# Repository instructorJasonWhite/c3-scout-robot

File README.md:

# C3 Scout Robot

A small rover built around an ESP32-C3 SuperMini, two N20 gearmotors, one 18650 cell and a printed chassis. Build it, drive it from a browser, and add animated OLED faces or a matching storage case.

**Start with the [Scout builder guide](https://mechatronicsaint.com/c3-scout/index.html).**

[The Build](https://mechatronicsaint.com/c3-scout/build.html) · [The Board](https://mechatronicsaint.com/c3-scout/board.html) · [The Code](https://mechatronicsaint.com/c3-scout/code.html) · [The Accessories](https://mechatronicsaint.com/c3-scout/accessories.html)

## Current release

The four-part builder guide was published **21 October 2026**. The [complete robot wiring diagram](https://mechatronicsaint.com/c3-scout/build.html#complete-wiring) was added **25 October 2026**, with an [editable SVG](docs/builder-guide/assets/wiring/scout-complete-wiring.svg).

| Area | Current edition |
| --- | --- |
| Mechanics and printed robot parts | Rev B, all M3 hardware |
| Electronics and factory files | Carrier C v10 / Silk 03 |
| Browser control firmware | 19 October 2026 · SCOUT 2 / protocol 2 |
| Optional Android app | 1.2.0 |
| ScoutFaces Arduino library | 1.0.0 · ten animated expressions |
| Storage cases | Bumper, OLED and ESP32-CAM · all v8 |

Latest installation check: **27 October 2026**. The published 19 October firmware uploaded and started successfully, with browser control and OLED available, zero motor targets and both saved reverse flags retained. This was an upload/startup check. See the [Code guide](https://mechatronicsaint.com/c3-scout/code.html#last-device-check) and [recorded status](verification/Scout-Startup-Check-2026-10-27.json).

## Browse or download

GitHub displays HTML files as source. Use the live guide above for illustrated instructions, or clone/download this repository and run the following from its root:

```sh
python -m http.server 8000
```

Open [the local guide](http://localhost:8000/index.html). Keep the full folder layout together so images, downloads and technical references work offline.

- [Current firmware and software ZIP](06-Scout-Control/Scout-Control-Web-2026-10-19.zip) — firmware images, editable source, tests, technical guide and optional Android APK.
- [Complete technical control guide](https://mechatronicsaint.com/c3-scout/06-Scout-Control/CONTROL-GUIDE.html) — wiring, setup, protocol, calibration and recorded checks.
- [ScoutFaces 1.0.0 ZIP](06-Scout-Control/ScoutFaces-1.0.0.zip) — install in Arduino with **Sketch → Include Library → Add .ZIP Library**.
- [ScoutFaces source](libraries/ScoutFaces/) and complete [AutoCycle](libraries/ScoutFaces/examples/AutoCycle/AutoCycle.ino) / [SelectExpression](libraries/ScoutFaces/examples/SelectExpression/SelectExpression.ino) examples.

Each case package includes editable Fusion and STEP models, STL parts, Bambu P1S PLA projects, previews and print notes. Use the matching latch for the chosen variant.

| v8 case | Complete download | Native Fusion | STL and 3MF files |
| --- | --- | --- | --- |
| Bumper | [ZIP](08-Storage-Cases/Bumper/Scout-Bumper-Case-v8-Thin-Walls.zip) | [F3D](08-Storage-Cases/Bumper/Scout-Bumper-Case-v8.f3d) | [Files and print guide](08-Storage-Cases/Bumper/) |
| OLED | [ZIP](08-Storage-Cases/OLED/Scout-OLED-Case-v8-Thin-Walls.zip) | [F3D](08-Storage-Cases/OLED/Scout-OLED-Case-v8.f3d) | [Files and print guide](08-Storage-Cases/OLED/) |
| ESP32-CAM | [ZIP](08-Storage-Cases/ESP32-CAM/Scout-ESP32-CAM-Case-v8-Thin-Walls.zip) | [F3D](08-Storage-Cases/ESP32-CAM/Scout-ESP32-CAM-Case-v8.f3d) | [Files and print guide](08-Storage-Cases/ESP32-CAM/) |

## Load the firmware and drive

1. **Open RUN before connecting ESP USB.** Keep RUN open while programming or charging.
2. Install Arduino ESP32 core 3.x. Select **ESP32C3 Dev Module** and enable **USB CDC On Boot**.
3. Install **WebSockets 2.7.2**, Adafruit SSD1306/GFX and their dependencies, plus ScoutFaces. Follow [The Code](https://mechatronicsaint.com/c3-scout/code.html) for the matching build and upload instructions. The production sketch is [firmware/ScoutDrive](firmware/ScoutDrive/).
4. After uploading, unplug ESP USB, lift the wheels for the direction check, then close RUN.
5. Join Scout's Wi-Fi, open **http://192.168.4.1/** and press **Connect**. Start with the default 35% drive limit. Release the joystick to send zero; press **Stop** to end control. Reload the browser after updating firmware.

Motor directions are saved on the ESP. This Scout was tested with both reverse switches ON; a fresh or erased board defaults both OFF. Check directions with the wheels lifted and save the appropriate settings.

Browser control sends commands every 100 ms and has a 1000 ms ESP command cutoff. After command loss, motors may continue for up to one second. The optional Android app retains its 400 ms cutoff. Opening RUN cuts motor power independently of software.

## Editable software and documentation

Use the top-level folders for ongoing development:

| Source | Contents |
| --- | --- |
| [firmware/](firmware/) | Production ESP32-C3 sketch, embedded browser controller, OLED sketches and host tests |
| [libraries/ScoutFaces/](libraries/ScoutFaces/) | Reusable animated-face library and both examples |
| [android/](android/) | Optional native Android app and controller tests |
| [scripts/](scripts/) | Build, upload, packaging and verification helpers |
| [docs/](docs/) | Control notes and editable builder-guide content under `builder-guide/` |

[06-Scout-Control/source/](06-Scout-Control/source/) is the frozen source copy for the published 19 October software release. Its files accompany the downloadable guide and package. The top-level source folders are the canonical editable copies; release copies should be refreshed together when publishing another release.

Build helpers accept local tool paths where supported. See the guide and script parameters for the required Arduino, Java, Android and host-test tools. Building firmware does not upload it.

## Hardware files

| Folder | Contents |
| --- | --- |
| [01-Electronics-CarrierC](01-Electronics-CarrierC/) | Current schematic, board, library, PDFs, sourcing workbook and electrical checks; historical reviews are marked |
| [02-Mechanical-RevB](02-Mechanical-RevB/) | Full rover, chassis and populated mechanical board in Fusion and STEP formats |
| [03-Print-STL](03-Print-STL/) | Robot print parts, print notes and M3 fastener list |
| [04-Component-References](04-Component-References/) | Manufacturer datasheets, reference geometry and source notes |
| [05-Factory-CarrierC-v10](05-Factory-CarrierC-v10/) | Matching Gerbers, BOM, placement files and factory upload guide |
| [07-Bumper-Options](07-Bumper-Options/) | Optional OLED and ESP32-CAM bumper prototypes |
| [08-Storage-Cases](08-Storage-Cases/) | All three v8 case releases |

## Prototype status and provenance

Carrier C's electrical component placement has not been synchronized into the populated Rev B mechanical model. Check actual module, connector and fastener clearances before fabrication. Full v8 case fit and the optional bumper mounts still require physical verification. The ESP32-CAM mount includes no camera firmware or Scout camera power/control integration.

The factory guide records the checked Carrier C v10 release; use its matching files together. Electrical protection, motor stall current, supply startup and temperature still require prototype qualification. The circuit has no charge-and-run load sharing.

[PROJECT-MANIFEST.json](PROJECT-MANIFEST.json) records the published project files, hashes and revision status; [CURRENT-RELEASE.json](CURRENT-RELEASE.json) summarizes the editions. Manufacturer PDFs and reference models retain their original ownership. The Pololu model is a generic N20-family reference rather than verified geometry for the purchased Coliao motors; see [reference notes](04-Component-References/REFERENCE-NOTES.txt). No project-wide license has been selected.

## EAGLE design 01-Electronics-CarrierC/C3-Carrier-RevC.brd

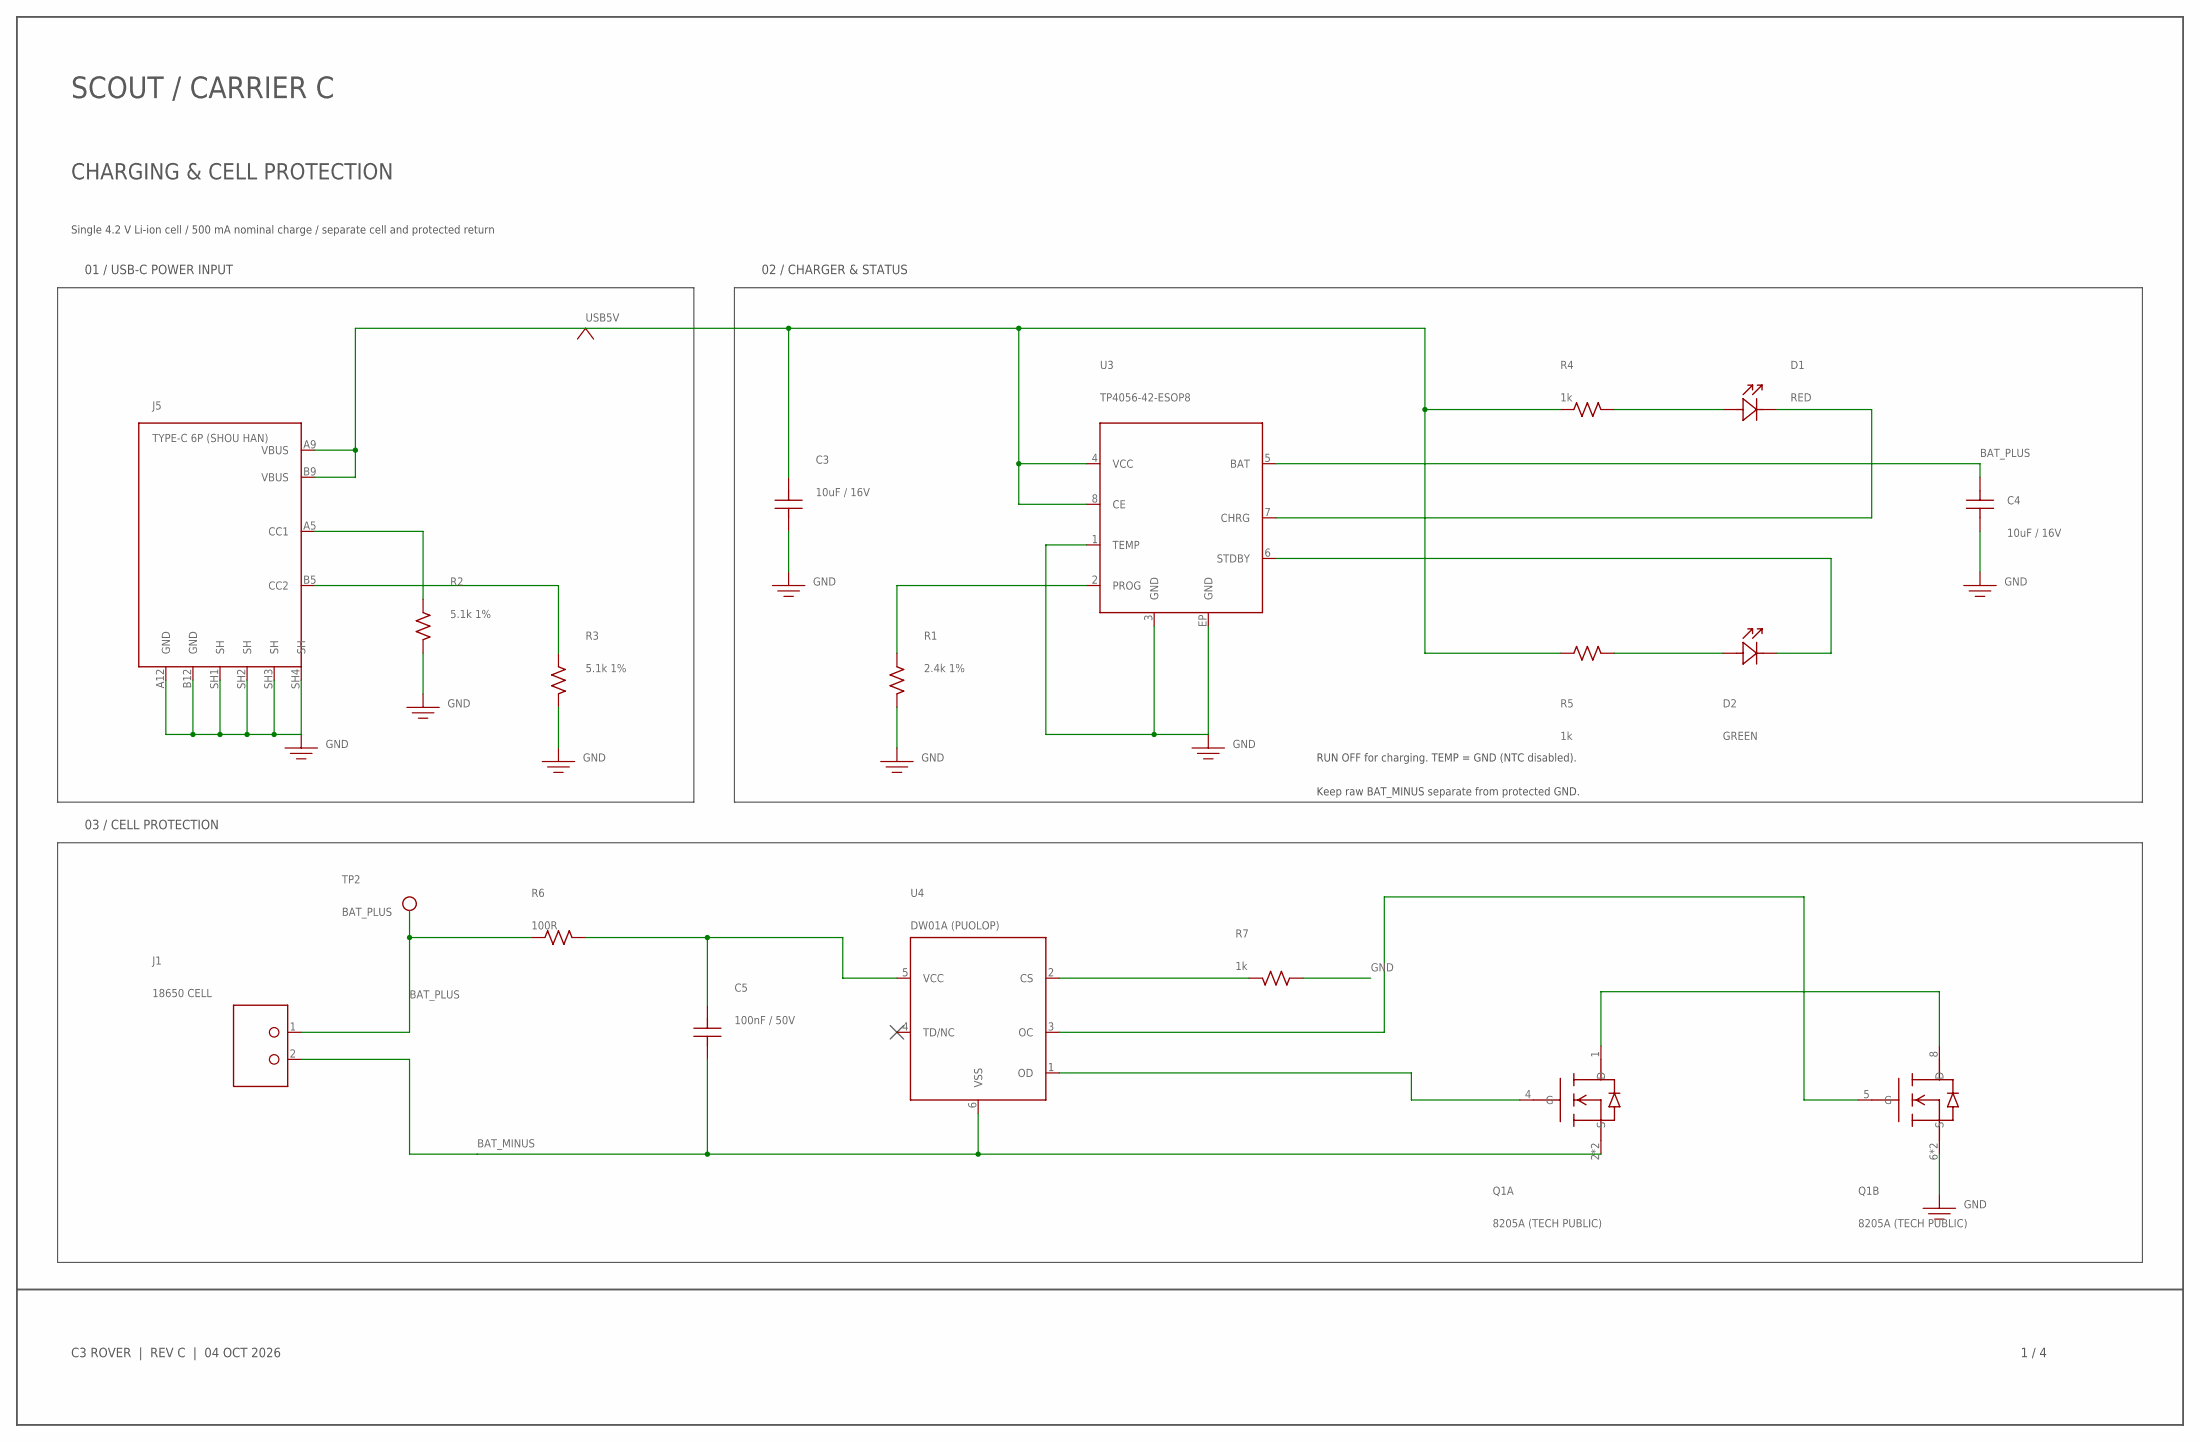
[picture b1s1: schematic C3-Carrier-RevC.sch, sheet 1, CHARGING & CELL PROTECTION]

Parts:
C3, C4: 10uF / 16V; C1206
C5: 100nF / 50V; C0805
D1: RED; LED0805
D2: GREEN; LED0805
J1: 18650 CELL; WIRE2-3.5
J5: TYPE-C 6P (SHOU HAN); USB-C-SHOUHAN-6P-C456012
Q1: 8205A (TECH PUBLIC); TSSOP8-0.65
R1: 2.4k 1%; R0805
R2, R3: 5.1k 1%; R0805
R4, R5, R7: 1k; R0805
R6: 100R; R0805
TP2: BAT_PLUS; TESTPAD
U3: TP4056-42-ESOP8; ESOP8-EP
U4: DW01A (PUOLOP); SOT23-6

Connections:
BAT_MINUS: C5.2, J1.2, Q1.2 (S), Q1.3 (S), U4.6 (VSS)
BAT_PLUS: C4.1, J1.1, R6.1, TP2.1, U3.5 (BAT); also elsewhere on the board
CC1: J5.A5 (CC1), R2.1
CC2: J5.B5 (CC2), R3.1
CHRG: D1.2, U3.7 (CHRG)
CHRG_LED: D1.1, R4.2
CS: R7.2, U4.2 (CS)
D12: Q1.1 (D), Q1.8 (D)
DW_VCC: C5.1, R6.2, U4.5 (VCC)
FULL_LED: D2.1, R5.2
GND: C3.2, C4.2, J5.A12 (GND), J5.B12 (GND), J5.SH1 (SH), J5.SH2 (SH), J5.SH3 (SH), J5.SH4 (SH), Q1.6 (S), Q1.7 (S), R1.2, R2.2, R3.2, R7.1, U3.1 (TEMP), U3.3 (GND), U3.EP (GND); also elsewhere on the board
OC: Q1.5 (G), U4.3 (OC)
OD: Q1.4 (G), U4.1 (OD)
PROG: R1.1, U3.2 (PROG)
STDBY: D2.2, U3.6 (STDBY)
USB5V: C3.1, J5.A9 (VBUS), J5.B9 (VBUS), R4.1, R5.1, U3.4 (VCC), U3.8 (CE)

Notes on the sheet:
SCOUT / CARRIER C
CHARGING & CELL PROTECTION
Single 4.2 V Li-ion cell / 500 mA nominal charge / separate cell and protected return
C3 ROVER | REV C | 04 OCT 2026
1 / 4
01 / USB-C POWER INPUT
02 / CHARGER & STATUS
03 / CELL PROTECTION
RUN OFF for charging. TEMP = GND (NTC disabled).
Keep raw BAT_MINUS separate from protected GND.

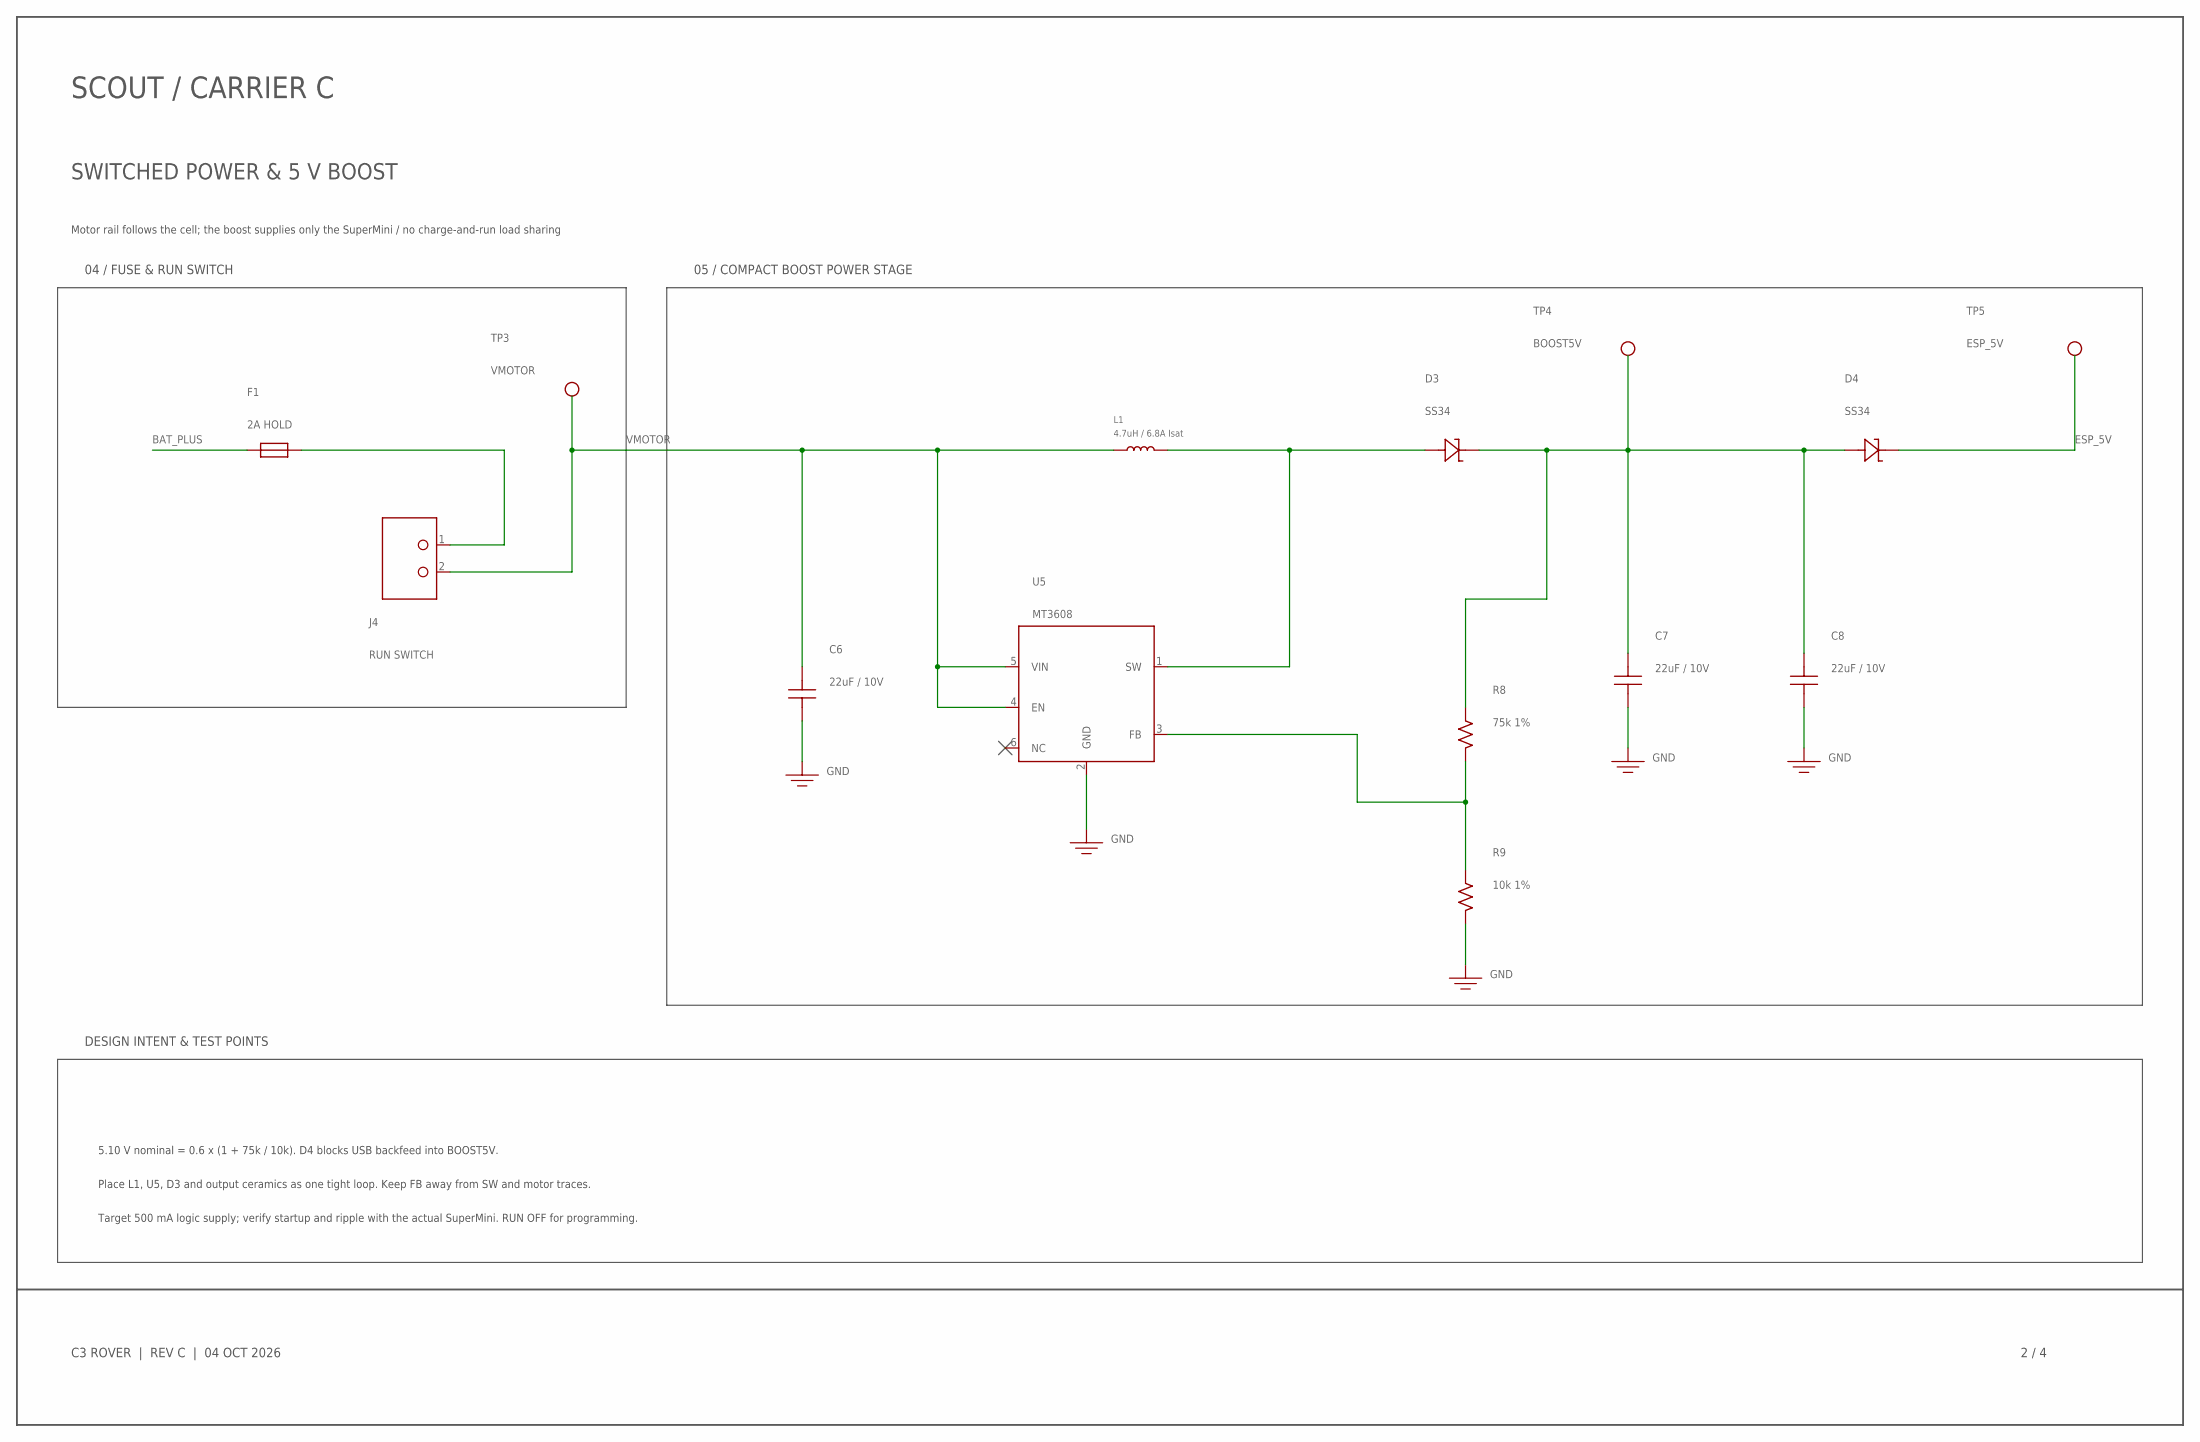
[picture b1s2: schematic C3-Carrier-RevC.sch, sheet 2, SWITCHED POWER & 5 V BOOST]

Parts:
C6, C7, C8: 22uF / 10V; C1206
D3, D4: SS34; SMA
F1: 2A HOLD; F1812
J4: RUN SWITCH; WIRE2-3.5
L1: 4.7uH / 6.8A Isat; L6
R8: 75k 1%; R0805
R9: 10k 1%; R0805
TP3: VMOTOR; TESTPAD
TP4: BOOST5V; TESTPAD
TP5: ESP_5V; TESTPAD
U5: MT3608; SOT23-6

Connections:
BAT_PLUS: F1.1; also elsewhere on the board
BOOST5V: C7.1, C8.1, D3.1, D4.2, R8.1, TP4.1
ESP_5V: D4.1, TP5.1; also elsewhere on the board
FB: R8.2, R9.1, U5.3 (FB)
FUSED_BAT: F1.2, J4.1
GND: C6.2, C7.2, C8.2, R9.2, U5.2 (GND); also elsewhere on the board
SW: D3.2, L1.2, U5.1 (SW)
VMOTOR: C6.1, J4.2, L1.1, TP3.1, U5.4 (EN), U5.5 (VIN); also elsewhere on the board

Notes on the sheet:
SCOUT / CARRIER C
SWITCHED POWER & 5 V BOOST
Motor rail follows the cell; the boost supplies only the SuperMini / no charge-and-run load sharing
C3 ROVER | REV C | 04 OCT 2026
2 / 4
04 / FUSE & RUN SWITCH
05 / COMPACT BOOST POWER STAGE
DESIGN INTENT & TEST POINTS
5.10 V nominal = 0.6 x (1 + 75k / 10k). D4 blocks USB backfeed into BOOST5V.
Place L1, U5, D3 and output ceramics as one tight loop. Keep FB away from SW and motor traces.
Target 500 mA logic supply; verify startup and ripple with the actual SuperMini. RUN OFF for programming.

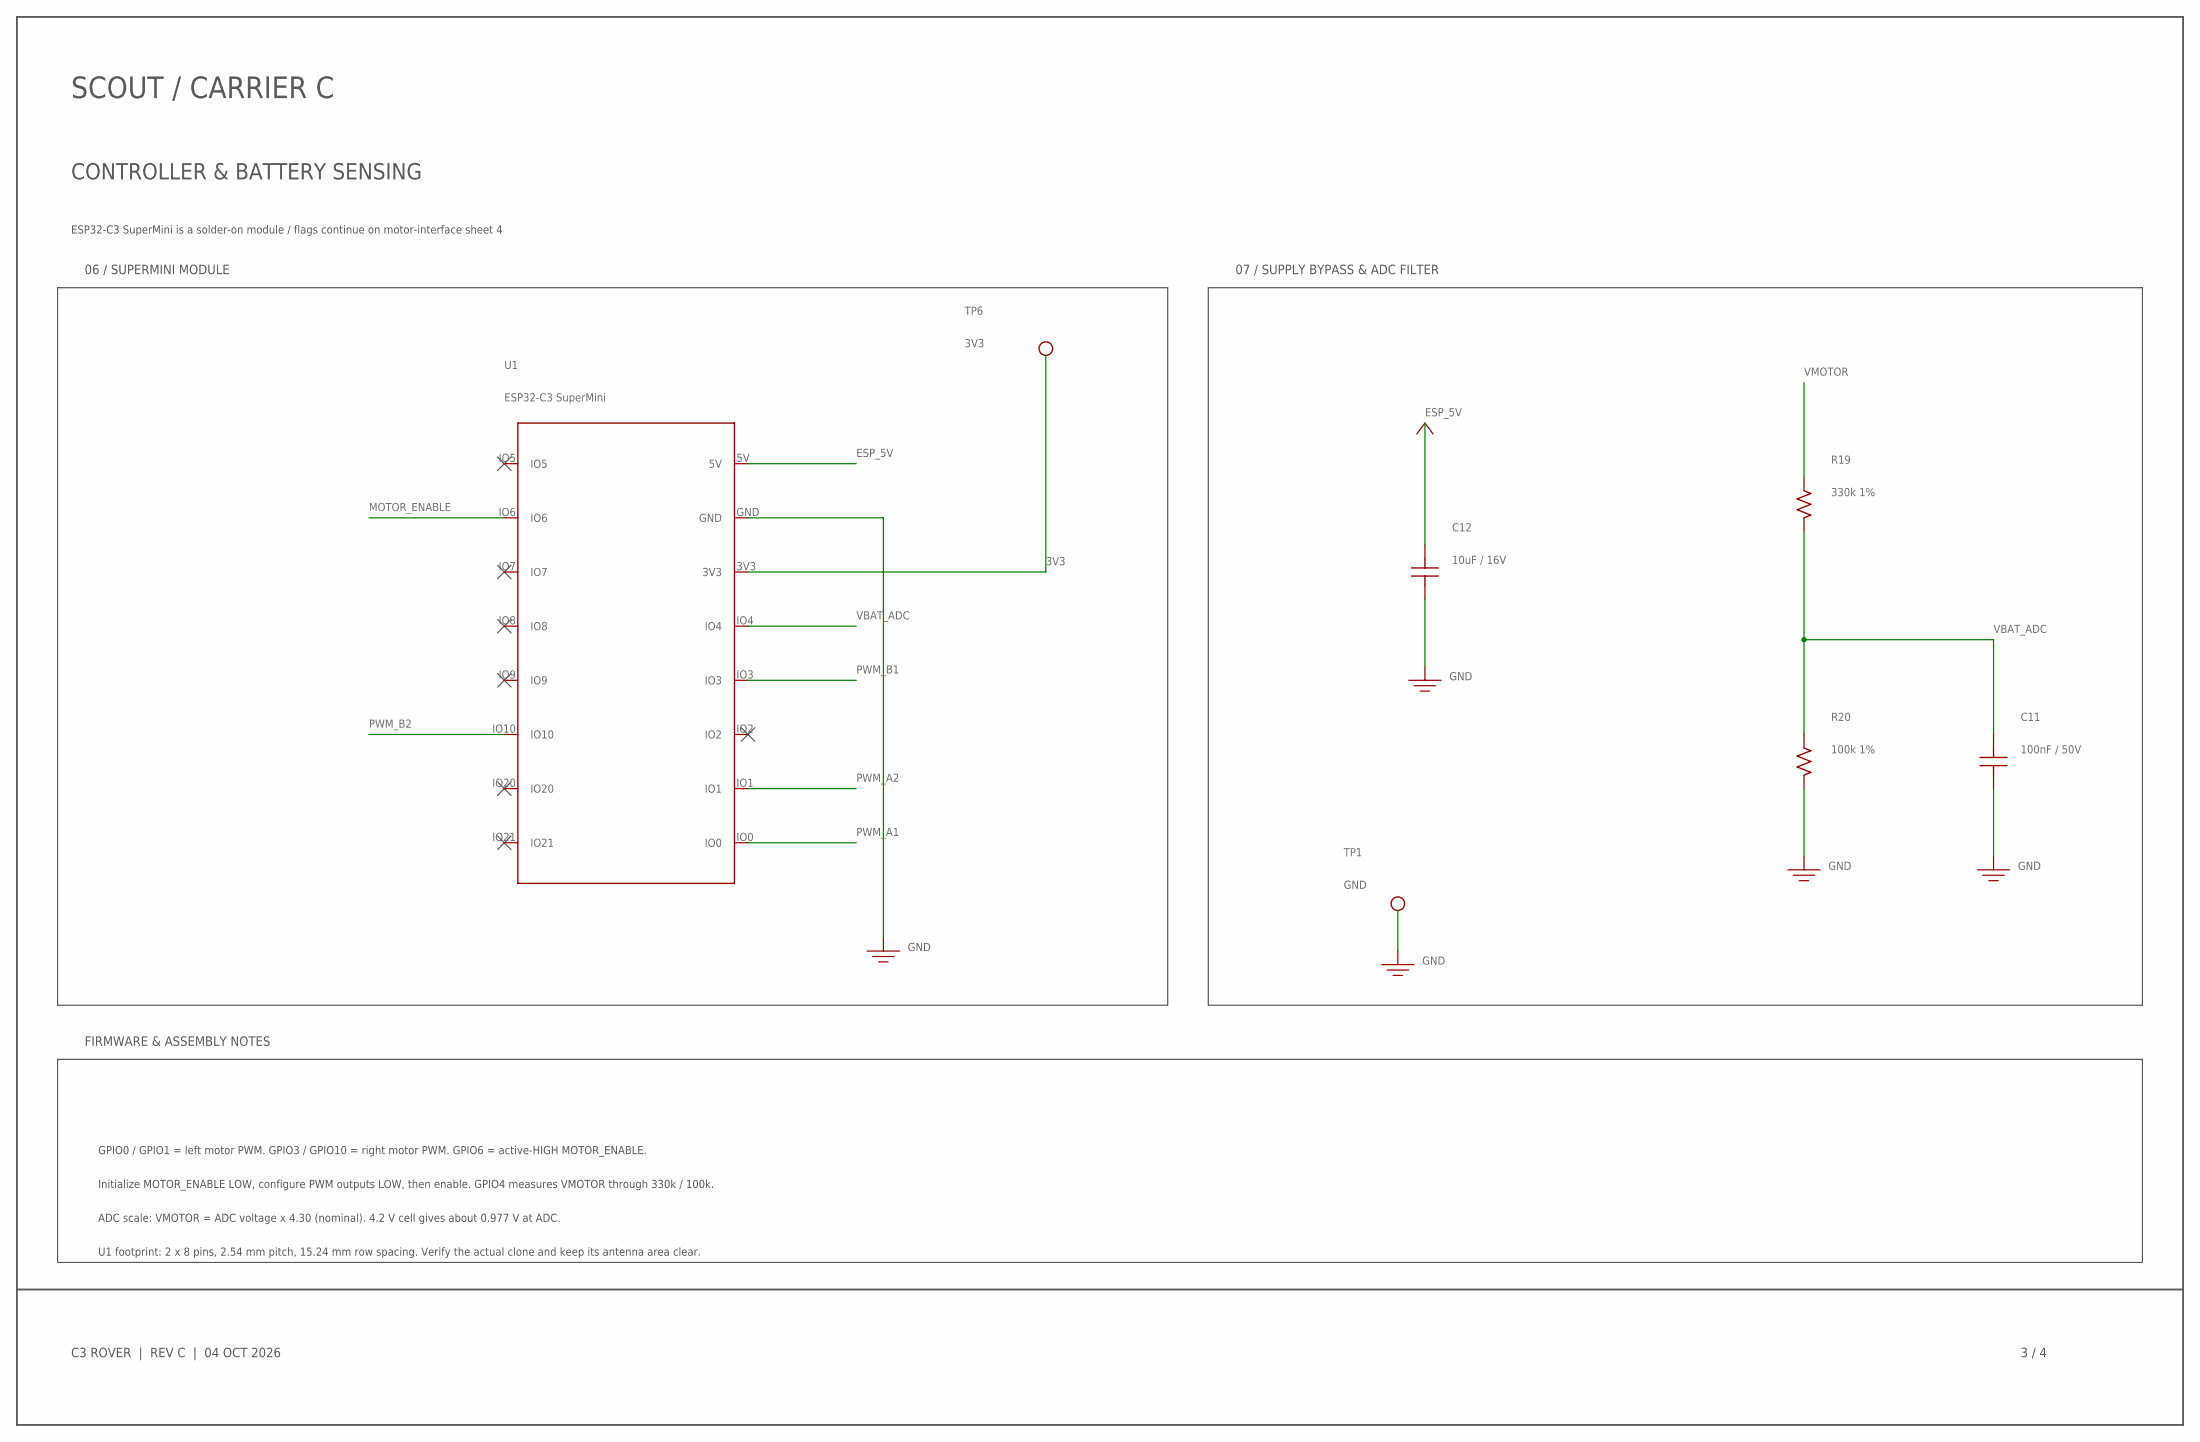
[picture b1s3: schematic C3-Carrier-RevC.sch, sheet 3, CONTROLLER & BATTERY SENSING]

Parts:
C11: 100nF / 50V; C0805
C12: 10uF / 16V; C1206
R19: 330k 1%; R0805
R20: 100k 1%; R0805
TP1: GND; TESTPAD
TP6: 3V3; TESTPAD
U1: ESP32-C3 SuperMini; SUPERMINI-2X8-15.24

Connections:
3V3: TP6.1, U1.3V3; also elsewhere on the board
ESP_5V: C12.1, U1.5V; also elsewhere on the board
GND: C11.2, C12.2, R20.2, TP1.1, U1.GND; also elsewhere on the board
MOTOR_ENABLE: U1.IO6; also elsewhere on the board
PWM_A1: U1.IO0; also elsewhere on the board
PWM_A2: U1.IO1; also elsewhere on the board
PWM_B1: U1.IO3; also elsewhere on the board
PWM_B2: U1.IO10; also elsewhere on the board
VBAT_ADC: C11.1, R19.2, R20.1, U1.IO4
VMOTOR: R19.1; also elsewhere on the board

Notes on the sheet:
SCOUT / CARRIER C
CONTROLLER & BATTERY SENSING
ESP32-C3 SuperMini is a solder-on module / flags continue on motor-interface sheet 4
C3 ROVER | REV C | 04 OCT 2026
3 / 4
06 / SUPERMINI MODULE
07 / SUPPLY BYPASS & ADC FILTER
FIRMWARE & ASSEMBLY NOTES
GPIO0 / GPIO1 = left motor PWM. GPIO3 / GPIO10 = right motor PWM. GPIO6 = active-HIGH MOTOR_ENABLE.
Initialize MOTOR_ENABLE LOW, configure PWM outputs LOW, then enable. GPIO4 measures VMOTOR through 330k / 100k.
ADC scale: VMOTOR = ADC voltage x 4.30 (nominal). 4.2 V cell gives about 0.977 V at ADC.
U1 footprint: 2 x 8 pins, 2.54 mm pitch, 15.24 mm row spacing. Verify the actual clone and keep its antenna area clear.

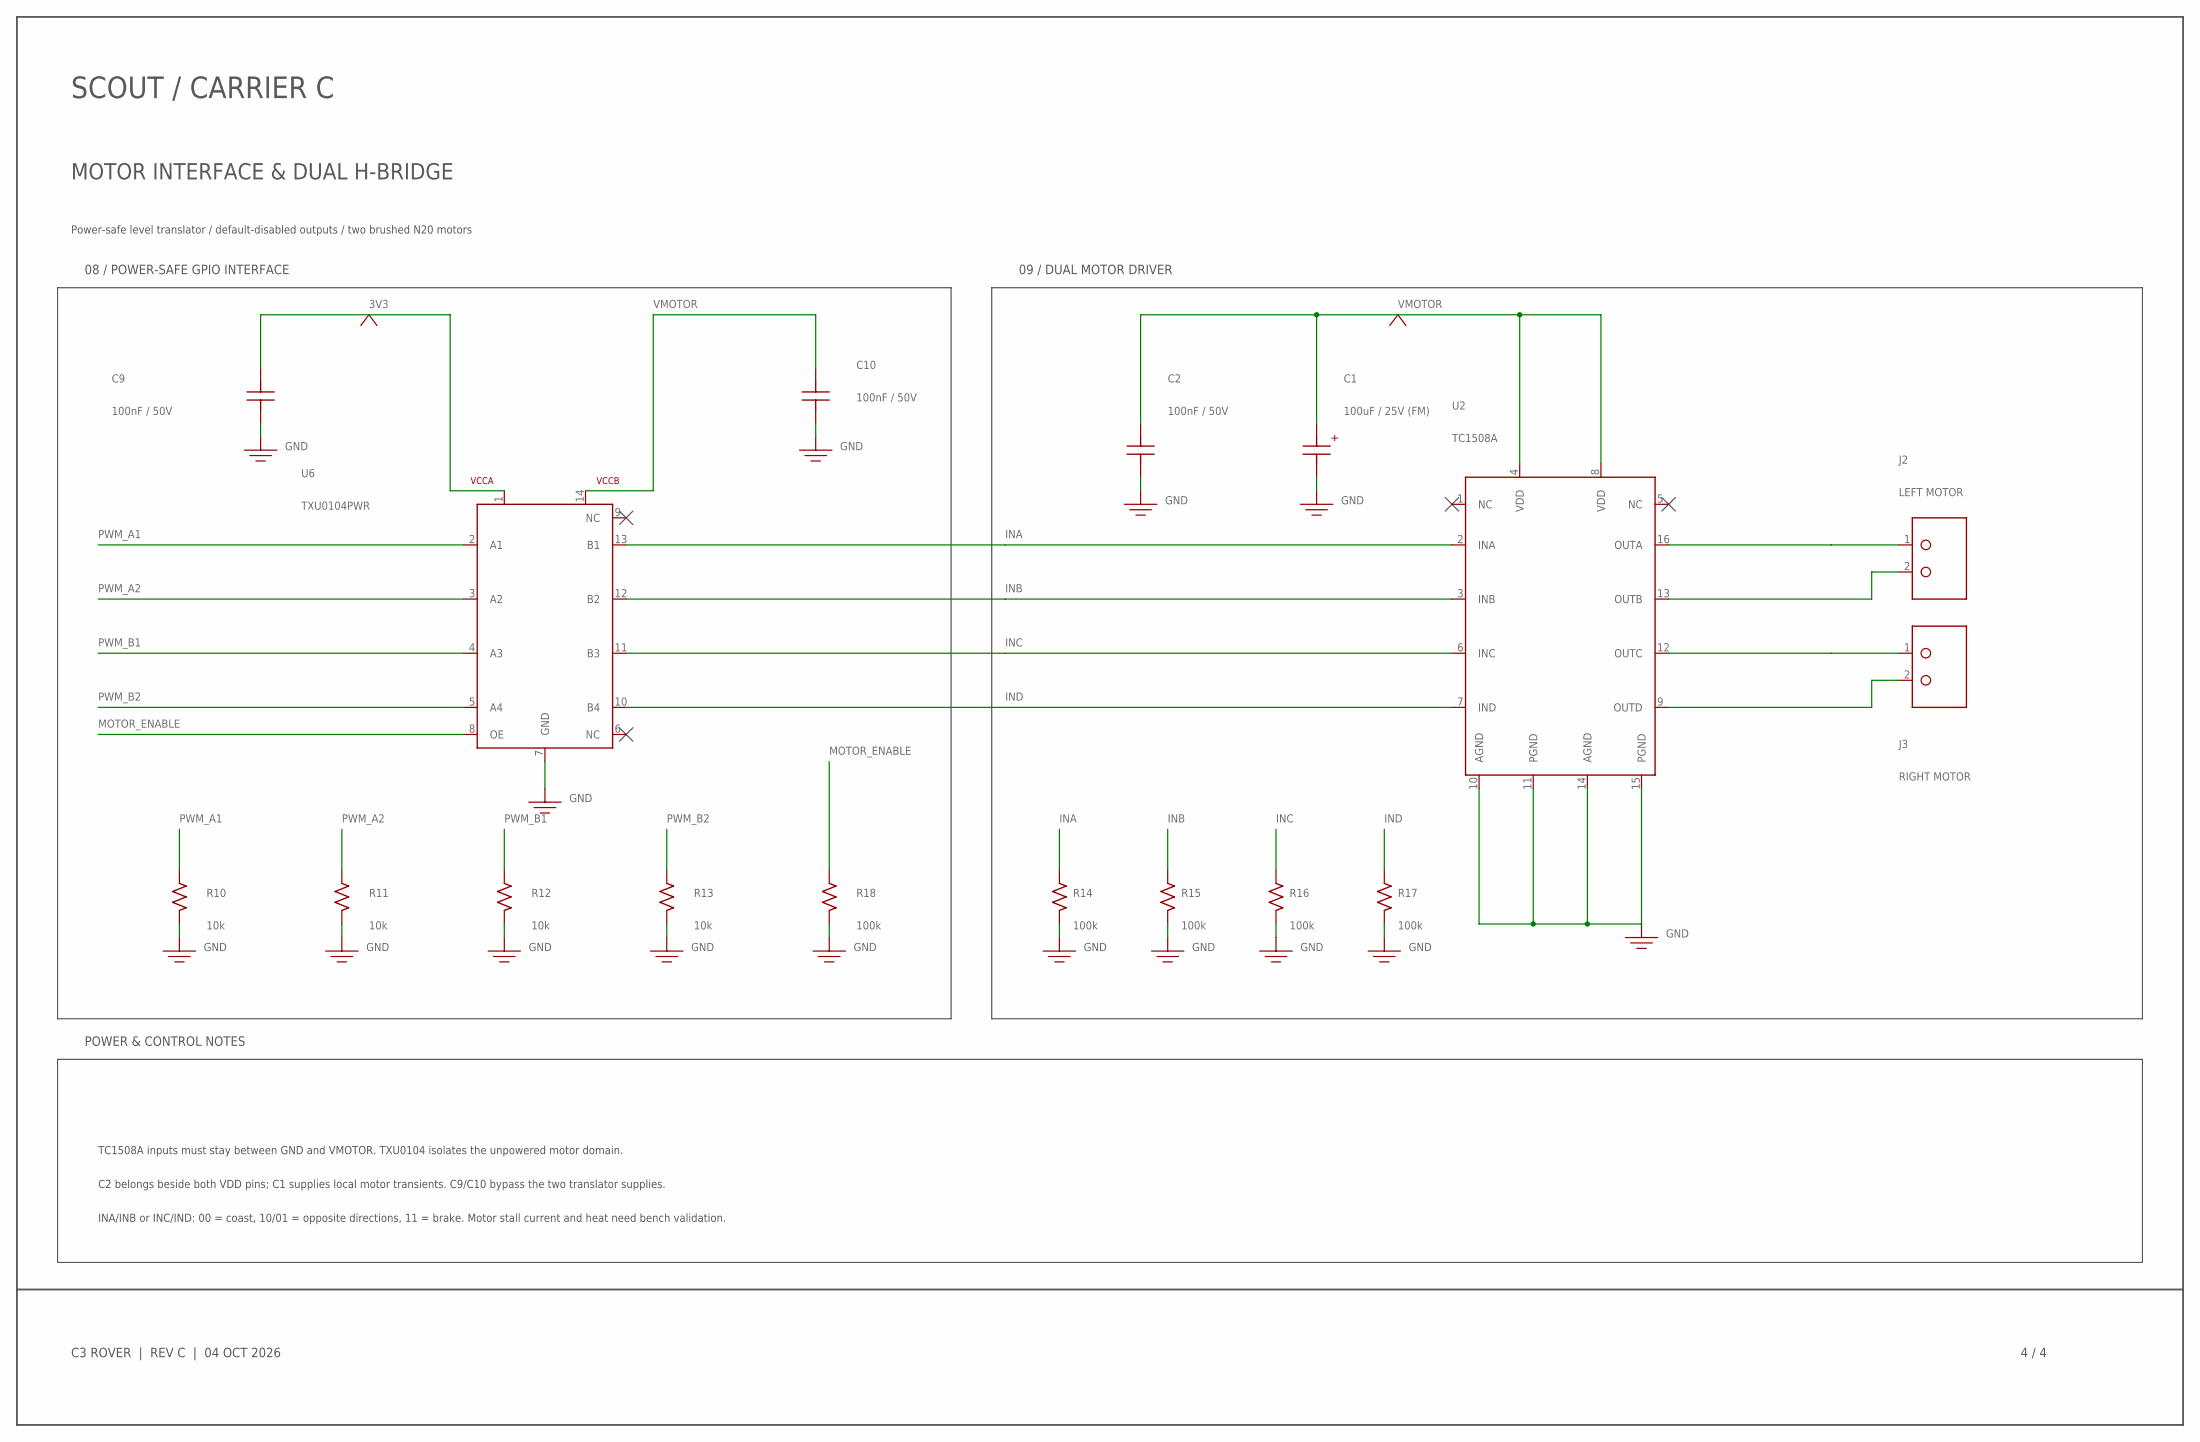
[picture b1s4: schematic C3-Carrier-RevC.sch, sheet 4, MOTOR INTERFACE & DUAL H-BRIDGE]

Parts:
C1: 100uF / 25V (FM); RADIAL-6.3-2.5
C2, C9, C10: 100nF / 50V; C0805
J2: LEFT MOTOR; WIRE2-3.5
J3: RIGHT MOTOR; WIRE2-3.5
R10, R11, R12, R13: 10k; R0805
R14, R15, R16, R17, R18: 100k; R0805
U2: TC1508A; SOIC16-1.27
U6: TXU0104PWR; TSSOP14-0.65

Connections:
3V3: C9.1, U6.1 (VCCA); also elsewhere on the board
GND: C1.2, C2.2, C9.2, C10.2, R10.2, R11.2, R12.2, R13.2, R14.2, R15.2, R16.2, R17.2, R18.2, U2.10 (AGND), U2.11 (PGND), U2.14 (AGND), U2.15 (PGND), U6.7 (GND); also elsewhere on the board
INA: R14.1, U2.2 (INA), U6.13 (B1)
INB: R15.1, U2.3 (INB), U6.12 (B2)
INC: R16.1, U2.6 (INC), U6.11 (B3)
IND: R17.1, U2.7 (IND), U6.10 (B4)
MOTOR_A1: J2.1, U2.16 (OUTA)
MOTOR_A2: J2.2, U2.13 (OUTB)
MOTOR_B1: J3.1, U2.12 (OUTC)
MOTOR_B2: J3.2, U2.9 (OUTD)
MOTOR_ENABLE: R18.1, U6.8 (OE); also elsewhere on the board
PWM_A1: R10.1, U6.2 (A1); also elsewhere on the board
PWM_A2: R11.1, U6.3 (A2); also elsewhere on the board
PWM_B1: R12.1, U6.4 (A3); also elsewhere on the board
PWM_B2: R13.1, U6.5 (A4); also elsewhere on the board
VMOTOR: C1.1, C2.1, C10.1, U2.4 (VDD), U2.8 (VDD), U6.14 (VCCB); also elsewhere on the board

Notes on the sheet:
SCOUT / CARRIER C
MOTOR INTERFACE & DUAL H-BRIDGE
Power-safe level translator / default-disabled outputs / two brushed N20 motors
C3 ROVER | REV C | 04 OCT 2026
4 / 4
08 / POWER-SAFE GPIO INTERFACE
09 / DUAL MOTOR DRIVER
POWER & CONTROL NOTES
TC1508A inputs must stay between GND and VMOTOR. TXU0104 isolates the unpowered motor domain.
C2 belongs beside both VDD pins; C1 supplies local motor transients. C9/C10 bypass the two translator supplies.
INA/INB or INC/IND: 00 = coast, 10/01 = opposite directions, 11 = brake. Motor stall current and heat need bench validation.

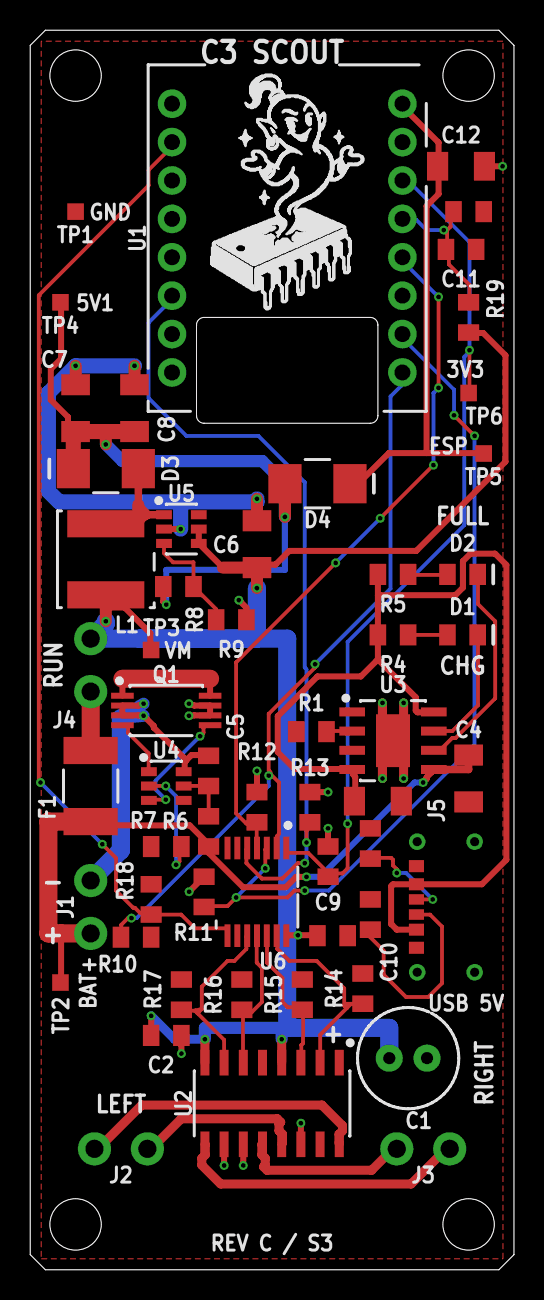
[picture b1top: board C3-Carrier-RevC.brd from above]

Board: 2 copper layers, 32.0 x 82.0 mm, 56 parts (0 on the bottom side), 37 nets.

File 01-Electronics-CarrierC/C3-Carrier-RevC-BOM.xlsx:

Carrier C sourcing BOM
46 fitted components / 45 factory assembly / 1 user module / reviewed 2026-10-05
Catalog listings are not stock reservations. JLC placement rotations require as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
References | Qty | Specification | Package | Manufacturer | MPN | LCSC / JLC code | Assembly category | Availability evidence |  | Source | Assembly notes
U1 | 1 | ESP32-C3 SuperMini | 2 x 8 / 2.54 mm | User module | ESP32-C3 SuperMini |  | Hand solder | User supplied |  |  | Verify clone pinout and 15.24 mm row spacing. Antenna over cutout; component si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
U2 | 1 | Dual motor driver | SOP-16 | Shenzhen Fuman | TC1508A | C5142992 | Extended | JLC catalog confirmed; stock not verified |  | https://jlcpcb.com/partdetail/Shenzhen_FumanElec-TC1508A/C5142992 | Validate actual N20 stall current and package temperature.
U3 | 1 | 500 mA charger | ESOP-8 with exposed pad | Top Power | TP4056-42-ESOP8 | C16581 | Extended | JLC catalog confirmed; stock not verified |  | https://jlcpcb.com/partdetail/TP4056-42-ESOP8/C16581 | R1 = 2.4 kohm. RUN OFF while charging. TEMP grounded; no cell-temperature sensi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
U4 | 1 | Cell protection | SOT-23-6 | PUOLOP | DW01A | C351410 | Extended | JLC stock verified 2026-10-05; user selected |  | https://jlcpcb.com/partdetail/DW01A/C351410 | Pin-compatible SOT-23-6; 2.5 V cutoff / 2.9 V recovery, 150 mV current sense. A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
Q1 | 1 | Dual common-drain N-MOSFET | TSSOP-8 | TECH PUBLIC | 8205A | C7419210 | Extended | JLC stock verified 2026-10-05; user selected |  | https://jlcpcb.com/partdetail/TECHPUBLIC-8205A/C7419210 | TSSOP-8, common drain at pins 1/8. Lower RDS(on) raises overcurrent trip curren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
U5 | 1 | 5.10 V boost | SOT-23-6 | Aerosemi | MT3608 | C84817 | Extended | JLC catalog confirmed; stock not verified |  | https://jlcpcb.com/partdetail/C84817 | Nominal 0.6 x (1 + 75k/10k). D4 drop precedes SuperMini 5V input.
U6 | 1 | 4-channel level translator | TSSOP-14 | Texas Instruments | TXU0104PWR | C2938871 | Extended | JLC catalog confirmed; stock not verified |  | https://jlcpcb.com/partdetail/TexasInstruments-TXU0104PWR/C2938871 | OE pulled low; separates 3V3 control from switched motor domain.
L1 | 1 | 4.7 uH / 4.5 A Irms / 6.8 A Isat | 6 x 6 x 4.5 mm max | Bourns | SRN6045TA-4R7M | C2044594 | Extended | JLC catalog confirmed; stock not verified |  | https://jlcpcb.com/partdetail/BOURNS-SRN6045TA4R7M/C2044594 | Manufacturer land pattern: 5.1 x 1.8 mm pads, 4.7 mm centers. Footprint updated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
D3, D4 | 2 | SS34 / 3 A / 40 V | SMA | MDD | SS34 | C8678 | Basic | JLC catalog confirmed; stock not verified |  | https://jlcpcb.com/partdetail/Mdd-SS34/C8678 | Pad 1 = cathode.
F1 | 1 | 2 A hold / 16 V PTC | 1812 | Littelfuse | 1812L200/16DR | C439873 | Extended | JLC catalog confirmed; stock not verified |  | https://jlcpcb.com/partdetail/Littelfuse-1812L20016DR/C439873 | 3.5 A trip rating; temperature derating applies.
D1 | 1 | Red indicator | 0805 | NationStar | NCD0805R1 | C84256 | Basic | JLC catalog confirmed; stock not verified |  | https://jlcpcb.com/partdetail/NCD0805R1/C84256 | Footprint pad 1 = anode; verify assembly-library rotation.
D2 | 1 | Green indicator | 0805 | Kento | KT-0805G | C2297 | Basic | JLC catalog confirmed; stock not verified |  | https://jlcpcb.com/partdetail/Hubei_KentoElec-KT0805G/C2297 | Footprint pad 1 = anode; verify assembly-library rotation.
C1 | 1 | 100 uF / 25 V / low impedance | Radial 6.3 x 11.2 mm; 2.5 mm pitch | Panasonic | EEUFM1E101 | C713389 | THT assembly | JLC: 1130 in stock; 1097 orderable on 2026-10-05 |  | https://jlcpcb.com/partdetail/PANASONIC-EEUFM1E101/C713389 | FM substitutes FR: same 100 uF/25 V, 6.3 x 11.2 mm, 2.5 mm pitch, 455 mA ripple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
C2, C5, C9, C10, C11 | 5 | 100 nF / 50 V / X7R / 10% | 0805 | Samsung | CL21B104KBCNNNC | C1711 | Catalog | JLC catalog confirmed; stock not verified |  | https://jlcpcb.com/partdetail/CL21B104KBCNNNC/C1711
C3, C4, C12 | 3 | 10 uF / 16 V / X7R / 10% | 1206 | Murata | GRM31CR71C106KA12L | C97954 | Extended | JLC catalog confirmed; stock not verified |  | https://jlcpcb.com/partdetail/MurataElectronics-GRM31CR71C10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
C6, C7, C8 | 3 | 22 uF / 10 V / X7R / 20% | 1206 | KEMET | C1206C226M8RACTU | C2167682 | Extended | JLC catalog confirmed; stock not verified |  | https://jlcpcb.com/partdetail/KEMET-C1206C226M8RACTU/C2167682 | Confirm effective capacitance under DC bias when qualifying the boost supply.
R1 | 1 | 2.4 kohm / 1% / 0.125 W | 0805 | UNI-ROYAL | 0805W8F2401T5E | C17526 | Verify | LCSC catalog confirmed; JLC availability unverified |  | https://www.lcsc.com/product-detail/C17526.html
R2, R3 | 2 | 5.1 kohm / 1% / 0.125 W | 0805 | UNI-ROYAL | 0805W8F5101T5E | C27834 | Basic | JLC catalog confirmed; stock not verified |  | https://jlcpcb.com/partdetail/0805W8F5101T5E/C27834
R4, R5, R7 | 3 | 1 kohm / 1% / 0.125 W | 0805 | UNI-ROYAL | 0805W8F1001T5E | C17513 | Basic | JLC catalog confirmed; stock not verified |  | https://jlcpcb.com/partdetail/0805W8F1001T5E/C17513
R6 | 1 | 100 ohm / 1% / 0.125 W | 0805 | UNI-ROYAL | 0805W8F1000T5E | C17408 | Basic | JLC catalog confirmed; stock not verified |  | https://jlcpcb.com/partdetail/0805W8F1000T5E/C17408
R8 | 1 | 75 kohm / 1% / 0.125 W | 0805 | UNI-ROYAL | 0805W8F7502T5E | C17819 | Verify | LCSC catalog confirmed; JLC availability unverified |  | https://www.lcsc.com/product-detail/C17819.html
R9, R10, R11, R12, R13 | 5 | 10 kohm / 1% / 0.125 W | 0805 | UNI-ROYAL | 0805W8F1002T5E | C17414 | Basic | JLC catalog confirmed; stock not verified |  | https://jlcpcb.com/partdetail/0805W8F1002T5E/C17414
R14, R15, R16, R17, R18, R20 | 6 | 100 kohm / 1% / 0.125 W | 0805 | UNI-ROYAL | 0805W8F1003T5E | C149504 | Basic | JLC catalog confirmed; stock not verified |  | https://jlcpcb.com/partdetail/0805W8F1003T5E/C149504
R19 | 1 | 330 kohm / 1% / 0.125 W | 0805 | UNI-ROYAL | 0805W8F3303T5E | C17629 | Verify | LCSC catalog confirmed; JLC availability unverified |  | https://www.lcsc.com/product-detail/C17629.html
J5 | 1 | USB-C charging inlet | USB-C-SHOUHAN-6P-C456012 | SHOU HAN | TYPE-C 6P | C456012 | Extended | JLC stock verified 2026-10-05; user selected |  | https://jlcpcb.com/partdetail/C456012 | 6-contact power-only 5 V / 3 A. Footprint updated in Fusion board v9: four 0.60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
J1, J2, J3, J4 | 4 | Battery / motors / RUN switch | 2-wire solder pads, 3.5 mm pitch | PCB feature | No fitted connector |  | PCB feature | No purchased component |  |  | J4 connects to external switch rated at least 3 A DC. Harness is outside carrie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
TP1, TP2, TP3, TP4, TP5, TP6 | 6 | Rail test point | 1.1 mm exposed pad | PCB feature | Test pad |  | PCB feature | No purchased component
